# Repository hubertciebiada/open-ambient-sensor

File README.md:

<h1 align="center">OAS — Open Ambient Sensor</h1>

<p align="center">
  <b>DIY multi-sensor environmental monitor for indoor spaces.</b><br>
  Measures air quality and presence; mounts on a standard wall-recessed electrical box; runs ESPHome and integrates natively with Home Assistant.
</p>

<p align="center">

</p>

https://github.com/user-attachments/assets/d60150c3-3ed5-4fff-b437-b9b54c48e413

---

## Status

**v0.54 — manufactured, bench-validated and in use.** Boards of this revision were fabricated and SMT-assembled at JLCPCB, brought up on the bench with a repeatable per-unit check, and run in a multi-unit deployment as the sensor input for Home Assistant HVAC automations. Working on the delivered hardware: the 24 V power chain, the Sensirion SEN66 (CO₂ / PM / VOC / NOx / T / RH, with Sensirion's STAR temperature compensation running inside the module), the HLK-LD2410C presence radar including stillness detection, the LED ring, Wi-Fi / OTA / native Home Assistant API, the Bluetooth proxy and the on-device web dashboard. The firmware reports `project_version: v0.54`, matching the version printed on the silkscreen. The design is fully script-generated and verified: `build.py` 35/35 stages PASS, DRC 0 violations / 0 unconnected, JLCPCB DFM 0 Danger on both the bare-board and assembly checks. The production files for this revision are attached to the [GitHub release](https://github.com/hubertciebiada/open-ambient-sensor/releases). See [`CLAUDE.md`](./CLAUDE.md) for the design rationale, hard constraints and the lessons learned along the way.

---

## Can I build one today?

**Yes — this revision has been built and works.** What to know before ordering:

- **The production files are in the repo.** [`hardware/output/jlcpcb/`](./hardware/output/jlcpcb/) holds the gerber + drill bundle, the BOM and the CPL files for JLCPCB SMT assembly (also attached to the GitHub release); they are regenerated and verified by the 35-stage pipeline on every build. Follow the ordering workflow in [`CLAUDE.md`](./CLAUDE.md#jlcpcb-ordering-workflow-distilled-from-v040-saga) — in particular the pre-payment Assembly Order cross-check, which has caught wrong-part substitutions more than once.
- **Seven components are hand-soldered after assembly** — the 24 V terminal block, the two ESP32-C6-DevKitM-1 socket headers, the LD2410C header and the three THT capacitors — and the SEN66 is attached with its JST GH lead and zip ties. Flashing and Home Assistant onboarding are documented in [`firmware/README.md`](./firmware/README.md).
- **Cost positioning.** OAS deliberately sits above bargain-DIY BOM cost: a calibrated Sensirion SEN66 combo sensor, an mmWave radar with stillness detection, and a commercial-grade injection-moulded enclosure are all premium choices made on purpose — see [Design philosophy](#design-philosophy). If lowest possible cost is your priority, other open-source projects optimise for that instead.

**Known limitations** (findings on the built units):

- **The LED ring effect is weaker than designed.** For the SEN66 to read correctly inside the enclosure, an air duct has to guide room air from the perforated cover to the sensor inlet, and that duct sits in front of part of the ring. The duct is not part of this repository yet.
- **Detecting a sleeping person relies on the presence timeout**, not on the radar's still-target thresholds — see the notes in [`firmware/esphome/packages/presence.yaml`](./firmware/esphome/packages/presence.yaml).
- **v0.51 prototype boards** need the pin overrides in [`firmware/esphome/HARDWARE-COMPAT-v0.51.md`](./firmware/esphome/HARDWARE-COMPAT-v0.51.md); v0.54 boards run the firmware defaults.

A consolidated step-by-step build guide is not written yet; open work is tracked in the [TODO list](./CLAUDE.md#open-work--todo) in `CLAUDE.md`.

---

## What it measures

- **Air quality** — CO₂, PM1 / PM2.5 / PM4 / PM10, VOC index, NOx index, temperature, relative humidity (Sensirion SEN66)
- **Occupancy / presence** — mmWave radar with stillness detection (HiLink HLK-LD2410C)

## Additional features

- 7× SK6812-SIDE RGB AQI ring with breathing effect (7 LEDs on an 8-slot ring; D13 vacated for the J1 24 V terminal); colour reflects an aggregated air-quality index
- **Bluetooth proxy** — extends BLE range across the deployment for Home Assistant BLE integrations
- Qwiic / STEMMA QT expansion port — future sensors without a PCB respin

---

## Design philosophy

The open-source DIY space offers many indoor-air-quality projects. Most optimise aggressively for cost. **OAS holds two priorities non-negotiable**, even when the trade-off is a higher per-unit BOM than the cheapest alternatives:

1. **Measurement quality.** Sensor choices favour accuracy and long-term stability over price.
2. **Aesthetic acceptability.** The device is meant to live in inhabited rooms; a commercial-grade injection-moulded enclosure replaces the typical 3D-printed box.

Both compromises (cheap-but-inaccurate, accurate-but-ugly) are rejected. See [`CLAUDE.md`](./CLAUDE.md) for the full rationale and the hard constraints any change must clear.

---

## Hardware overview

| Function | Component | Interface |
|---|---|---|
| MCU | ESP32-C6-DevKitM-1-N4 (EAN 5904422385651) | 2× USB-C on module |
| Air quality combo | Sensirion SEN66-SIN-T | I²C (JST GH 6-pin cable) |
| Presence | HiLink HLK-LD2410C | UART @ 256000 baud |
| Visual indicator | 7× SK6812-SIDE side-emit ring (Ø26 mm base pitch, 8 slots with D13 vacated for J1) | 1-wire WS281x on GPIO 8 |
| Power input | 24 V DC terminal block + TVS + PTC + reverse-polarity P-FET | — |

**Enclosure:** SZOMK AK-N-94 (Ø128 mm perforated white ABS). PCB is a **Ø120 mm D-shape** with a flat chord along the bottom edge. Mounts on a standard wall-recessed electrical box (60 mm screw pitch).

Authoritative module metadata (EAN, MPN, datasheet URLs, derived dimensions) lives in [`hardware/kicad/boardgen/_project.py::EXTERNAL_MODULES`](./hardware/kicad/boardgen/_project.py). Pinout is in [`boardgen/_project.py::GPIO_ASSIGNMENTS`](./hardware/kicad/boardgen/_project.py). Full design rationale and hard constraints: [`CLAUDE.md`](./CLAUDE.md).

---

## Repository layout

```
open-ambient-sensor/
├── README.md                       # this file
├── CLAUDE.md                       # design rationale, hard constraints, working conventions
├── GPLv3-LICENSE.md
├── .gitignore
├── media/                          # promo video (oas-promo.mp4) + README photos (oas-*.webp)
├── firmware/
│   ├── README.md                   # flashing + Home Assistant integration
│   ├── esphome/
│   │   ├── oas.yaml                # top-level ESPHome config
│   │   ├── packages/               # core / leds / air-quality / presence / bt-proxy
│   │   └── examples/               # anonymized per-device override examples
│   ├── tools/                      # bringup_check.py — repeatable per-unit bench check
│   └── secrets.yaml.example
└── hardware/
    ├── kicad/
    │   ├── build.py                # THE single entrypoint — emits sources + runs the 35-stage pipeline
    │   ├── boardgen/               # source of truth — generators for every .kicad_* file
    │   ├── pipeline/               # 35 verification/export stages (generic / oas / jlcpcb)
    │   ├── tests/                  # unit-test suite (pytest; run by stage 16 of build.py)
    │   ├── tools/                  # manual-trigger scripts (route extract, DFM upload, jlcparts cache)
    │   ├── oas_routes.py           # routing snapshot (replayed onto the generated PCB)
    │   ├── lcsc_mapping.py         # SMD BOM — LCSC SKU source of truth
    │   └── oas.kicad_*             # generated KiCad project files (derived artefacts — never hand-edit)
    ├── renders/                    # generated previews (PNG + SVG, visual changelog)
    ├── photos/                     # photos of built units (EXIF stripped)
    └── output/                     # production deliverables (ibom + jlcpcb/ ZIP + BOM + 2× CPL)
```

---

## Rebuilding the design from source

The KiCad project is **fully script-generated**. The `.kicad_pcb` / `.kicad_sch` / `.kicad_pro` / library files are derived artefacts — **never hand-edit them**; the next build overwrites every edit. The source of truth lives in [`hardware/kicad/boardgen/`](./hardware/kicad/boardgen/) (Python generators), [`lcsc_mapping.py`](./hardware/kicad/lcsc_mapping.py) (SMD BOM), and [`oas_routes.py`](./hardware/kicad/oas_routes.py) (routing snapshot).

```sh
cd hardware/kicad
python build.py
```

`build.py` is the only top-level entrypoint. It regenerates every KiCad source file bit-identically (deterministic v5 UUIDs — an unchanged tree produces an empty `git diff`) and then runs the full 35-stage verification pipeline: DRC, ERC, determinism self-check, analytical DC / ampacity / boot-strap / thermal / I²C-rise-time checks, ngspice SPICE simulations (buck soft-start, IEC 61000-4-5 surge, reverse polarity), unit tests, renders, and the vendor export stages that produce the JLCPCB deliverables. Any stage failure aborts the build.

**Requirements:**

- Python 3.11+
- KiCad 10 with `kicad-cli` on `PATH`
- `pip install mypy pytest cairosvg pygerber`
- `git submodule update --init` (kicad-skip, InteractiveHtmlBom, jlcparts, and other tools under `hardware/kicad/third_party/`)
- One-time jlcparts offline cache for the LCSC part-verification stage: `python hardware/kicad/tools/setup_jlcparts_cache.py` (~2 GiB download, expands to a local SQLite cache)

ngspice and the vendor SPICE models are downloaded automatically into a gitignored `.tmp/` directory on first run. Individual pipeline stages are independently runnable for debugging (e.g. `python pipeline/generic/03_drc.py`), but a committable state always comes from a full `build.py` pass.

---

## Contributing

Contributions are welcome once the design stabilises. Any change must clear both design pillars (measurement quality, aesthetic acceptability) and the hard constraints listed in [`CLAUDE.md`](./CLAUDE.md#hard-constraints-do-not-violate-without-an-explicit-documented-decision).

**This is a public repository** — see the [public-repository rules](./CLAUDE.md#-public-repository-rules) for the anonymisation and third-party-IP requirements that apply to every committed file.

---

## License

GNU General Public License v3.0 — see [`GPLv3-LICENSE.md`](./GPLv3-LICENSE.md).

---

## References

- AirGradient ONE (open-source inspiration): <https://github.com/airgradienthq/arduino>
- Sensirion SEN66 product page: <https://sensirion.com/products/catalog/SEN66>
- HiLink LD2410 documentation: <https://www.hlktech.net>
- ESPHome documentation: <https://esphome.io>
- JLCPCB component library: <https://jlcpcb.com/parts>

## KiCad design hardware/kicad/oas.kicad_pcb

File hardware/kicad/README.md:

# KiCad project — OAS

Base KiCad 10.x project for the Open Ambient Sensor PCB. **Preliminary draft** — board outline and mounting holes only; schematic and routing are TODO.

## How to open

1. Install **KiCad 10.0.2** or newer from <https://www.kicad.org/download/>.
2. Open `oas.kicad_pro` in KiCad.
3. The project will load:
   - `oas.kicad_sch` — empty schematic (placeholder)
   - `oas.kicad_pcb` — board outline + 3 mounting holes on `Edge.Cuts`
   - Local footprint library `oas` (just the custom `MountingHole_3.8mm_M3` for now)

When KiCad opens the PCB the first time it may ask you to migrate the project — accept; the file format is already at v10.

## What's already in `oas.kicad_pcb`

- **Board outline on `Edge.Cuts`:** Ø120 mm circular arc (R=60 mm) + flat chord 82.65 mm (precise: 82.6545 mm from the DXF). Origin (0, 0) is the centre of the circle. The flat chord sits at Y≈+43.50 — in KiCad's coordinate convention (Y grows downward on screen), that's the visual **bottom** of the board.
- **3× M3 mounting holes (NPTH)**: Ø3.8 mm drill, no copper pad, on a pitch circle Ø110 mm. Positions:
  - H1: (+47.631, +27.500) — bottom-right
  - H2: (−47.631, +27.500) — bottom-left
  - H3: (0, −55.000) — top (opposite the chord)
- **Cable pass-through hole**: Ø12 mm circular cut-out on `Edge.Cuts` at the PCB centre (origin) — 24 V power wires enter from the rear of the case, pass through to a terminal block on the front side. Sized for 3× 1.5 mm² conductors with margin.
- **5× connector cutout keepout zones** on F.Cu + B.Cu blocking tracks, vias, pads, copperpour and footprints — one per case-wall cutout. See [`../case/README.md`](../case/README.md#connector-cutouts-in-the-case-wall-along-the-flat-chord) for the exact dimensions.
- **5× rectangle markers on `Dwgs.User`** labelled `C1…C5` with their size — visual reference for connector placement in pcbnew (this layer is not plotted).
- **Clock-face sector markers on `Dwgs.User`**: 3 dashed radial lines (12:00, 03:00, 09:00 azimuths) + 3 labels (`POWER`, `MCU`, `SENSORS`). Sectors map onto the hierarchical schematic sheets and define where each subsystem's components belong on the PCB. See [`../../docs/ARCHITECTURE.md`](../../docs/ARCHITECTURE.md#pcb-sector-layout) for the rationale.
- **Stackup:** 2-layer, FR-4 1.6 mm, 1 oz (35 µm) copper, white solder mask, black silkscreen, HASL lead-free finish.
- **JLCPCB-compatible design rules:** min trace/space 0.15 mm, min via 0.5 mm Ø / 0.3 mm drill, min hole 0.3 mm, edge clearance 0.3 mm.

## Material and stackup decisions (and why)

You said you've never done a PCB — here's the rationale for every choice. Anything below can be changed in `oas.kicad_pro` (design rules) or in `oas.kicad_pcb`'s `(setup (stackup ...))` block.

| Choice | Value | Why |
|---|---|---|
| **Layer count** | 2 | Sufficient for ESP32-C6 + I²C + UART + WS2812. 4-layer is overkill for this design and costs ~1.5× more at JLCPCB. Can be bumped if noise becomes an issue in v2. |
| **Board thickness** | 1.6 mm | JLCPCB default, free; mechanically rigid for a Ø120 mm board. |
| **Material** | FR-4, Tg ≥ 130 °C | JLCPCB Standard FR-4 (Tg 135–150). Fine for 24 V DC, low currents, no thermal stress. |
| **Copper weight** | 1 oz (35 µm) | JLCPCB default, free. Adequate for ≤ 3 A peak on power traces. |
| **Solder mask colour** | **White** | **Aesthetic match with the white perforated ABS enclosure** (CLAUDE.md design pillar 2 — aesthetic acceptability). White mask at JLCPCB costs a small premium over green but is worth it here. |
| **Silkscreen colour** | Black | Standard, high contrast on white mask. |
| **Surface finish** | HASL lead-free | JLCPCB default, free. ENIG would look nicer but adds ~$15 to a small batch and the pads aren't visible in the enclosure anyway. |
| **Min trace / space** | 0.15 mm (6 mil) | JLCPCB Standard rules. Going finer (4 mil) costs more without benefit on this design. |
| **Min via** | 0.5 mm Ø / 0.3 mm drill | JLCPCB Standard rules. |
| **Min hole** | 0.3 mm | JLCPCB Standard rules. |
| **Edge clearance** | 0.3 mm | JLCPCB tolerance for the routed board edge. |

If you want a quote, upload the gerbers (once generated — TODO) to <https://jlcpcb.com>. With these defaults the board falls in JLCPCB's cheapest tier (~$2–5 per unit at quantity 5–10, plus shipping).

## How to regenerate everything

The single entry point for any change is **`regenerate.py`**:

```bash
python regenerate.py
```

That script:
1. runs `generate.py` to rebuild every KiCad source file from the Python geometry constants;
2. runs `kicad-cli pcb drc` and `kicad-cli sch erc` (aborts on any error / warning);
3. re-renders every preview into `renders/`:
   - `2d-top.{svg,png}` — production-style top view (F.Cu + masks + silks + Edge.Cuts)
   - `2d-cutouts.{svg,png}` — Edge.Cuts + Dwgs.User cutout markers + F.Cu (no-go zones)
   - `2d-bottom.{svg,png}` — mirrored bottom view
   - `3d-top.png` — raytraced 3D render (~15 s)
   - `_drc.rpt` / `_erc.rpt` — text reports of DRC / ERC results

Typical run time: ~30 s (dominated by the 3D render).

**UUIDs are deterministic** (v5 namespaced under the OAS project), so re-running with no source changes produces a **bit-identical** `oas.kicad_pcb` — `git diff` is empty unless geometry actually changed.

### When to use `generate.py` directly

Almost never. `regenerate.py` is the canonical entry point. The one case where `generate.py` alone makes sense is if you want a quick smoke test of a `generate.py` change without paying for the 3D render.

### Changing geometry

Edit the constants at the top of `generate.py`:

- `R_OUTLINE`, `CHORD`, `HALF_CHORD` — PCB outline
- `HOLE_DIAMETER`, `PAD_DIAMETER`, `R_PITCH` — mounting holes
- `CUTOUTS` — list of `(name, x_min, x_max, y_min, y_max)` for the case-wall cutouts
- `PAGE_CENTRE_X`, `PAGE_CENTRE_Y` — page-space offset (you almost never want to change this)

For structural / material changes (layer count, stackup, design rules, footprint definitions), edit the relevant generator function further down in `generate.py`.

After editing, run `python regenerate.py` and commit the resulting diff (sources + KiCad files + renders together — they are one logical change).

The geometry constants currently match the SZOMK AK-N-94 manufacturer DXF (see [`../case/README.md`](../case/README.md)).

## Layout strategy

The PCB orientation in KiCad matches the physical wall-mount orientation:

- **Bottom edge** (flat chord, Y=+43.5) — connector strip: 24 V terminal, SWD header (unpopulated), Qwiic expansion (no external USB-C — DevKitM-1's onboard USB-C accessible before sealing)
- **Top half / sensors region** — SEN66 (PCB-mounted, face-up), LD2410 mmWave radar, NT3H2211 + NFC antenna
- **Middle** — MCU (ESP32-C6-DevKitM-1-N4, antenna toward 12:00) and status LED (onboard NeoPixel on GPIO 8)
- **Adjacent to the 24 V terminal** — power section (TVS, PTC, buck converters)

Thermal-isolation slots (1.5 mm milled gaps in FR4) will separate the Power, MCU and peripheral zones — to be drawn on `Edge.Cuts` once the floorplan is finalised.

See [`../../docs/ARCHITECTURE.md`](../../docs/ARCHITECTURE.md) for the full pinout and thermal/layout rationale.

## What you'll do next (TODO)

Roughly in order:

1. **Schematic** (`oas.kicad_sch`) — place the ESP32-C6-DevKitM-1-N4 (EAN 5904422385651), SEN66 connector, LD2410 connector, NT3H2211, buck converters, TVS, PTC, 24 V terminal block, SWD/UART recovery header (unpopulated), Qwiic connector. No external USB-C and no external WS2812 — both are on the DevKitM-1 module. Net them up.
2. **Footprints** — assign footprints in the schematic (most parts are stock in `Connector_*`, `Sensor_*`, `Package_DFN_QFN`, `Package_SO`). The mounting holes already use the custom `oas:MountingHole_3.8mm_M3`.
3. **PCB layout** — update PCB from schematic, then place parts respecting:
   - 17 mm front-side height limit (5 mm back-side with washer-lifted PCB)
   - SEN66 is **not on the PCB** (mounted on cover, JST GH cable to a header)
   - Connector strip along the flat chord
   - Thermal-isolation slots between zones
4. **Run DRC** at JLCPCB rules; fix violations.
5. **3D view** — check no component exceeds 17 mm.
6. **Generate gerbers** (`File → Fabrication Outputs → Gerbers`) into `../gerbers/`.

## Files in this directory

```
hardware/kicad/
├── README.md                                    # this file
├── generate.py                                  # script that built the project
├── oas.kicad_pro                                # project (design rules, net classes)
├── oas.kicad_sch                                # empty schematic
├── oas.kicad_pcb                                # PCB with outline + mounting holes
├── fp-lib-table                                 # registers the "oas" footprint library
├── sym-lib-table                                # empty symbol library table
└── libraries/
    └── oas.pretty/
        └── MountingHole_3.8mm_M3.kicad_mod      # custom footprint matching the DXF
```

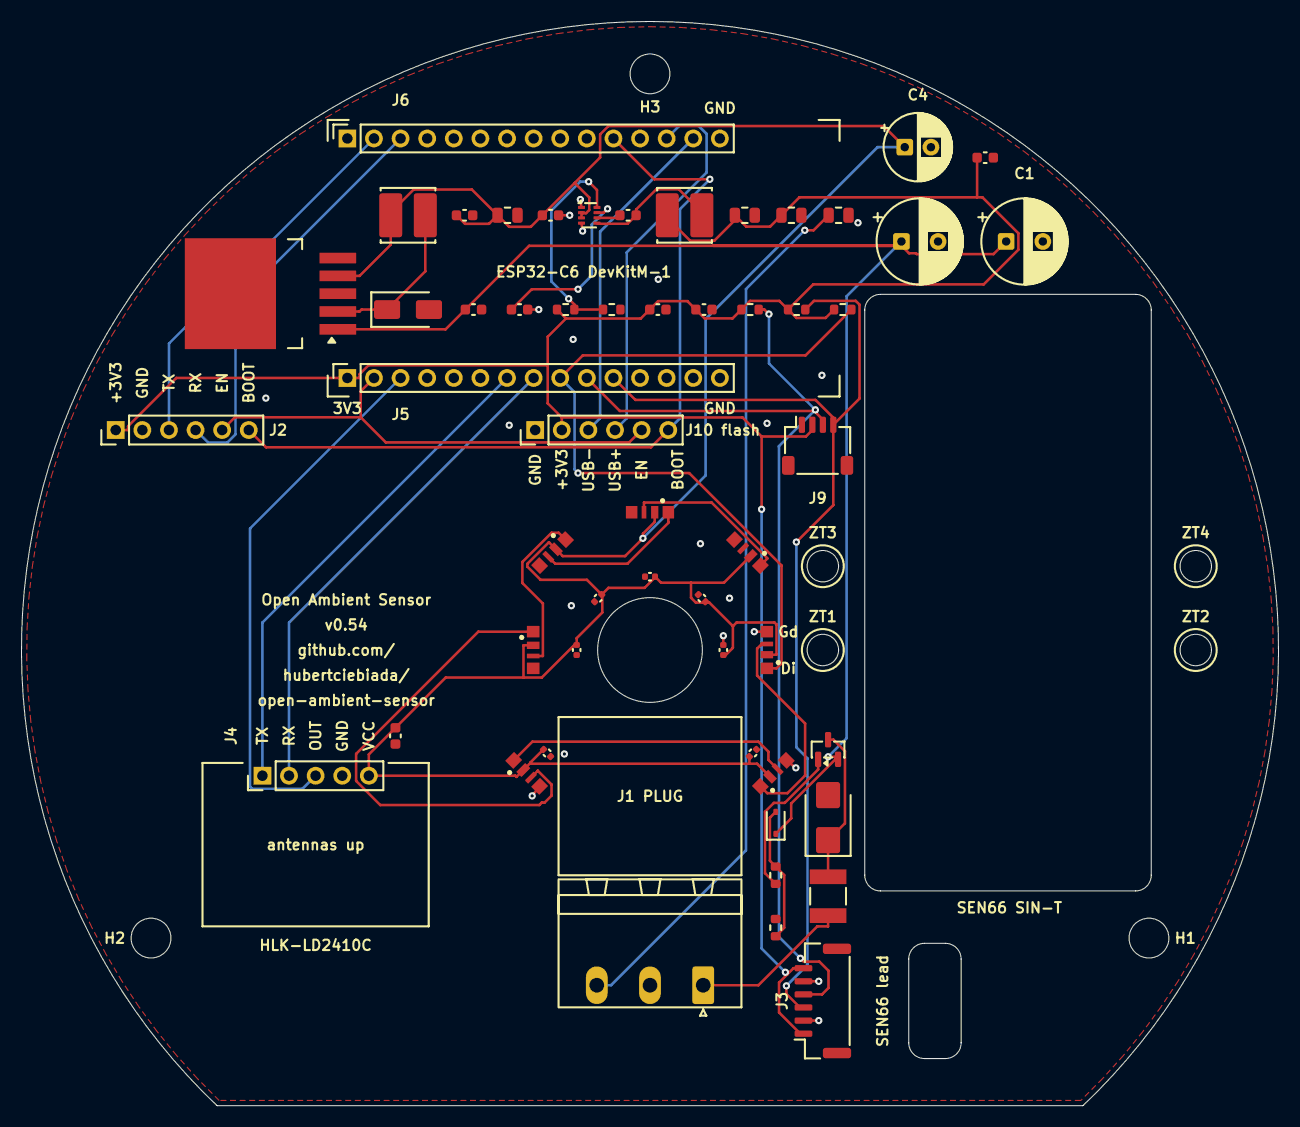
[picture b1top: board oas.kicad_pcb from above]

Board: 2 copper layers, 120.0 x 103.5 mm, 64 parts (0 on the bottom side), 32 nets.

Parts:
C1, C3: 100uF/50V; CP_Radial_D8.0mm_P3.50mm
C2: 10nF Y2; C_0805_2012Metric
C4: 220uF/10V; CP_Radial_D6.3mm_P2.50mm
C5, C9: 10uF; C_0805_2012Metric
C6: 22uF; C_0805_2012Metric
C7, C10, C11, C13, C14, C15, C16, C17: 100nF; C_0603_1608Metric
C8: 47nF; C_0603_1608Metric
C20, C21, C23, C24, C25, C26, C27: 100nF; C_0402_1005Metric
D1: SMBJ24A; D_SMB
D2: SS14; D_SMA
D3: 10V Zener 200mW; D_SOD-323
D11, D12, D14, D15, D16, D17, D18: SK6812-SIDE
F1: 1812L075/33DR; Fuse_1812L_4532Metric
H1, H2, H3: MountingHole_3.8mm_M3_NPTH; MountingHole_3.8mm_M3
J1: Phoenix_MSTBA_2,5/3-G-5,08 (24V input); PhoenixContact_MSTBA_2,5_3-G-5,08_1x03_P5.08mm_Horizontal
J2: UART/Boot Recovery (DNP); PinHeader_1x06_P2.54mm_Vertical
J3: JST SM06B-GHS-TB (SEN66 connector); JST_GH_SM06B-GHS-TB_1x06-1MP_P1.25mm_Horizontal
J4: 1x5 P2.54mm header (HLK-LD2410C); PinHeader_1x05_P2.54mm_Vertical
J5: ESP32 row A (pins 1..15, antenna-side row); PinSocket_1x15_P2.54mm_Vertical
J6: ESP32 row B (pins 16..30, USB-side row); PinSocket_1x15_P2.54mm_Vertical
J9: JST SM04B-SRSS-TB (Qwiic / Stemma QT); JST_SH_SM04B-SRSS-TB_1x04-1MP_P1.00mm_Horizontal
J10: Native-USB recovery (DNP); PinHeader_1x06_P2.54mm_Vertical
L1: 33uH; L_Cenker_CKCS5040
L2: 2.2uH; L_Cenker_CKCS5040
LDR1: LD2410_Mechanical_Reference
MOD1: oas:ESP32-C6-DevKitM-1_Reference; ESP32-C6-DevKitM-1_Reference
Q1: AO3401A; SOT-23
R1: 100k 1%; R_0603_1608Metric
R2: 100k; R_0603_1608Metric
R3: 30.9k; R_0603_1608Metric
R4: 1k; R_0603_1608Metric
R5, R6: 4.7k; R_0603_1608Metric
R7: 10k; R_0603_1608Metric
SENS1: SEN66_Mechanical_Reference
U1: LM2596S-5.0; TO-263-5_LM2596
U2: TPS62933; SOT-583-8
ZT1, ZT2, ZT3, ZT4: ZipTieHole_3mm_NPTH

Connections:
+3V3: C6.1, C9.1, C10.1, C16.1, C17.1, J2.1, J3.1, J3.6, J5.1, J9.2, J10.2, L2.1, R2.1, R5.1, R6.1, R7.1
+5V: C4.1, C5.1, C11.1, C14.1, C15.1, C20.1, C21.1, C23.1, C24.1, C25.1, C26.1, C27.1, D11.2, D12.2, D14.2, D15.2, D16.2, D17.2, D18.2, J4.5, L1.1, U1.4, U2.2, U2.3
+24V: C1.1, C3.1, C13.1, D3.1, Q1.2, U1.1
/IO/BOOT: J2.6, J6.11, J10.6
/IO/EN: J2.5, J5.2, J10.5
/IO/I2C_SCL: J3.3, J5.11, J9.4, R6.2
/IO/I2C_SDA: J3.4, J5.10, J9.3, R5.2
/IO/USB_DM: J6.14, J10.3
/IO/USB_DP: J6.13, J10.4
/MCU/LD2410_OUT: J4.3, J5.3
/MCU/LD2410_UART_RX: J4.1, J5.7
/MCU/LD2410_UART_TX: J4.2, J5.8
/MCU/UART_RX: J2.4, J6.3
/MCU/UART_TX: J2.3, J6.2
/MCU/WS2812_DIN: D11.1, J5.9, R7.2
Earth_Protective: C2.1, J1.3
GND: C1.2, C2.2, C3.2, C4.2, C5.2, C6.2, C8.2, C9.2, C10.2, C11.2, C13.2, C14.2, C15.2, C16.2, C17.2, C20.2, C21.2, C23.2, C24.2, C25.2, C26.2, C27.2, D1.2, D2.2, D11.4, D12.4, D14.4, D15.4, D16.4, D17.4, D18.4, J1.2, J2.2, J3.2, J3.5, J4.4, J5.13, J5.15, J6.1, J6.12, J6.15, J9.1, J10.1, R1.2, R3.2, U1.3, U1.5, U2.1, U2.4
unnamed: D1.1, F1.2, Q1.3
unnamed: D2.1, L1.2, U1.2
unnamed: D3.2, R1.1, R4.2
unnamed: D11.3, D12.1
unnamed: D12.3, D14.1
unnamed: D14.3, D15.1
unnamed: D15.3, D16.1
unnamed: D16.3, D17.1
unnamed: D17.3, D18.1
unnamed: F1.1, J1.1
unnamed: Q1.1, R4.1
unnamed: C7.1, U2.6
unnamed: R2.2, R3.1, U2.8
unnamed: C8.1, U2.7
unnamed: C7.2, L2.2, U2.5

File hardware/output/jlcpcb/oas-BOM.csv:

Comment,Designator,Footprint,Manufacturer,MPN,LCSC Part #,JLCPCB_Library,Qty
47nF,C8,C_0603_1608Metric,Samsung Electro-Mechanics,CL10B473KB8NNNC,C1622,Basic,1
100nF,"C7,C10,C11,C13,C14,C15,C16,C17",C_0603_1608Metric,Yageo,CC0603KRX7R9BB104,C14663,Basic,8
100nF,"C20,C21,C23,C24,C25,C26,C27",C_0402_1005Metric,Samsung Electro-Mechanics,CL05B104KO5NNNC,C1525,Basic,7
1k,R4,R_0603_1608Metric,UNI-ROYAL (Uniroyal Elec),0603WAF1001T5E,C21190,Basic,1
100k 1%,"R1,R2",R_0603_1608Metric,UNI-ROYAL (Uniroyal Elec),0603WAF1003T5E,C25803,Basic,2
100uF 50V,"C1,C3",CP_Radial_D8.0mm_P3.50mm,,,,THT (hand-solder),2
10k 1%,R7,R_0603_1608Metric,UNI-ROYAL (Uniroyal Elec),0603WAF1002T5E,C25804,Basic,1
10nF Y2,C2,C_0805_2012Metric,Murata Electronics,GRM21BR72A103KA01L,C97925,Extended,1
10uF 25V,"C5,C9",C_0805_2012Metric,Samsung Electro-Mechanics,CL21A106KAYNNNE,C15850,Basic,2
10V Zener 200mW,D3,D_SOD-323,Nanjing Semtech Electronics,BZT52C10S,C19334,Extended,1
1x15 P2.54 mm female socket (ESP32 J1 antenna-side row),J5,PinSocket_1x15_P2.54mm_Vertical,,,,THT (hand-solder),1
1x15 P2.54 mm female socket (ESP32 J3 USB-side row),J6,PinSocket_1x15_P2.54mm_Vertical,,,,THT (hand-solder),1
"1x5 P2.54mm through-hole header (HLK-LD2410C daughterboard, soldered)",J4,PinHeader_1x05_P2.54mm_Vertical,,,,THT (hand-solder),1
2.2uH 2A,L2,L_Cenker_CKCS5040,CENKER,CKCS5040-2.2uH/M,C354602,Extended,1
220uF 10V,C4,CP_Radial_D6.3mm_P2.50mm,,,,THT (hand-solder),1
22uF 10V,C6,C_0805_2012Metric,Samsung Electro-Mechanics,CL21A226MAQNNNE,C45783,Basic,1
30.9k 1%,R3,R_0603_1608Metric,UNI-ROYAL (Uniroyal Elec),0603WAF3092T5E,C23022,Extended,1
33uH 2A,L1,L_Cenker_CKCS5040,CENKER,CKCS5040-33uH/M,C354612,Extended,1
4.7k 1%,"R5,R6",R_0603_1608Metric,UNI-ROYAL (Uniroyal Elec),0603WAF4701T5E,C23162,Basic,2
AO3401A,Q1,SOT-23,Alpha & Omega Semiconductor,AO3401A,C15127,Extended,1
JST SH SM04B-SRSS-TB (Qwiic / Stemma QT),J9,JST_SH_SM04B-SRSS-TB_1x04-1MP_P1.00mm_Horizontal,JST Sales America,SM04B-SRSS-TB(LF)(SN),C160404,Extended,1
"JST SM06B-GHS-TB (SEN66-SIN-T, MPN 3.001.030; TME/Mouser)",J3,JST_GH_SM06B-GHS-TB_1x06-1MP_P1.25mm_Horizontal,JST Sales America,SM06B-GHS-TB(LF)(SN),C133065,Extended,1
LM2596S-5.0,U1,TO-263-5_LM2596,Texas Instruments,LM2596S-5.0/NOPB,C116713,Extended,1
"Phoenix_MSTBA_2,5/3-G-5,08",J1,"PhoenixContact_MSTBA_2,5_3-G-5,08_1x03_P5.08mm_Horizontal",,,,THT (hand-solder),1
PTC 750mA / 33V,F1,Fuse_1812L_4532Metric,Littelfuse,1812L075/33DR,C151170,Extended,1
SK6812-SIDE,"D11,D12,D14,D15,D16,D17,D18",SK6812-SIDE,OPSCO Optoelectronics,SK6812SIDE-A,C5378721,Extended,7
SMBJ24A,D1,D_SMB,Brightking,SMBJ24A,C87268,Basic,1
SS14,D2,D_SMA,MDD (Microdiode Semiconductor),SS14,C2480,Basic,1
TPS62933,U2,SOT-583-8,Texas Instruments,TPS62933DRLR,C3200405,Extended,1

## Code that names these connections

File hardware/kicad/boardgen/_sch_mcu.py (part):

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      the +3V3 bus / R5 / R6 / C9 / C17 wiring drop in unchanged.

      J2 (UART/Boot recovery, DNP) — rotated to angle=180 in v0.21
      so its UART TX/RX pin row aligns with J6's UART_TX (pin 2 at
      Y=125.73) / UART_RX (pin 3 at Y=123.19). At angle=180 the J2
      pin order in screen Y is REVERSED vs angle=0: pin 1 (+3V3) at
      the BOTTOM, pin 6 (BOOT) at the TOP.

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      J5 (DevKitM-1 J1, antenna-side header)
        J5.1   3V3                              → +3V3 bus
        J5.2   RST                              → hier label "EN"
        J5.3   GPIO2                            → hier label "LD2410_OUT"
        J5.4   GPIO3                            → no_connect (spare)
        J5.5   GPIO4   (strap MTMS)             → no_connect
        J5.6   GPIO5   (strap MTDI)             → no_connect
        J5.7   GPIO0                            → hier label "LD2410_UART_RX"
        J5.8   GPIO1                            → hier label "LD2410_UART_TX"
        J5.9   GPIO8   (strap boot, onboard LED)→ hier label "WS2812_DIN"
        J5.10  GPIO6                            → hier label "I2C_SDA"
        J5.11  GPIO7                            → hier label "I2C_SCL"
        J5.12  GPIO14                           → no_connect (spare)
        J5.13  GND                              → GND
        J5.14  5V                               → no_connect (powering 3V3 only)
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
      J6 (DevKitM-1 J3, USB-side header)
        J6.1   GND                              → GND
        J6.2   GPIO16  (U0TXD console)          → local label "UART_TX"
        J6.3   GPIO17  (U0RXD console)          → local label "UART_RX"
        J6.4   GPIO23                           → no_connect (spare)
        J6.5   GPIO22                           → no_connect (spare)
        J6.6   GPIO21                           → no_connect (spare)
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        J6.10  GPIO15  (strap)                  → no_connect
        J6.11  GPIO9   (strap, BOOT button)     → hier label "BOOT"
        J6.12  GND                              → GND
        J6.13  GPIO13  (USB D+)                 → hier label "USB_DP"
        J6.14  GPIO12  (USB D-)                 → hier label "USB_DM"
        J6.15  GND                              → GND

    Inter-sheet nets exported via hierarchical_label (matching sheet
    ports are declared on the root sheet's MCU sheet block):
      I2C_SDA, I2C_SCL    → sensors sub-sheet + io sub-sheet (Qwiic)
      LD2410_UART_TX/_RX  → sensors sub-sheet (LD2410C, J4 pins 2 / 1)
      LD2410_OUT          → sensors sub-sheet
      USB_DM, USB_DP      → io sub-sheet (J10 native-USB recovery header)
      EN                  → io sub-sheet (J10 chip-enable / reset pin)
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    EN net with the IO sub-sheet's J10 recovery EN pin):
      J2.1  +3V3
      J2.2  GND
      J2.3  UART_TX        — taps J6 pin 2 UART_TX
      J2.4  UART_RX        — taps J6 pin 3 UART_RX
      J2.5  EN             — hier label, joins J5 pin 2 RST
      J2.6  BOOT           — hier label, joins J6 pin 11 BOOT

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    # Per-signal pin-tip resolution (single source of truth).
    J5_3V3_Y    = j5_pin_y(J5_SIGNAL_PIN["3V3"])         # 92.71
    J5_RST_Y    = j5_pin_y(J5_SIGNAL_PIN["RST"])         # 95.25
    J5_LDR_Y    = j5_pin_y(J5_SIGNAL_PIN["LD2410_OUT"])  # 97.79
    J5_LD_RX_Y  = j5_pin_y(J5_SIGNAL_PIN["LD2410_UART_RX"])  # 107.95
    J5_LD_TX_Y  = j5_pin_y(J5_SIGNAL_PIN["LD2410_UART_TX"])  # 110.49
    J5_WS_Y     = j5_pin_y(J5_SIGNAL_PIN["WS2812_DIN"])  # 113.03
    J5_SDA_Y    = j5_pin_y(J5_SIGNAL_PIN["I2C_SDA"])     # 115.57
    J5_SCL_Y    = j5_pin_y(J5_SIGNAL_PIN["I2C_SCL"])     # 118.11
    J6_TX_Y     = j6_pin_y(J6_SIGNAL_PIN["UART_TX"])     # 125.73
    J6_RX_Y     = j6_pin_y(J6_SIGNAL_PIN["UART_RX"])     # 123.19
    J6_BOOT_Y   = j6_pin_y(J6_SIGNAL_PIN["BOOT"])        # 102.87
    J6_USB_DP_Y = j6_pin_y(J6_SIGNAL_PIN["USB_DP"])      # 97.79
    J6_USB_DM_Y = j6_pin_y(J6_SIGNAL_PIN["USB_DM"])      # 95.25

    # ===== C9: bulk decoupling, 10uF ceramic (non-polarized) =====
    # Reviewer raised C9's voltage rating from 10 V to 16 V (v0.5):
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    R5_Y = 80.01                    # body center; pin1 = 76.20, pin2 = 83.82
    R6_Y = 80.01

    # ===== R7: GPIO 8 (WS2812_DIN) boot-strap pull-up, 10 kΩ 0603 =====
    # v0.22 — new in this revision (Task #18 M2). ESP32-C6 GPIO 8 is a
    # strap pin that must be HIGH at boot for SPI flash boot mode. The
    # DevKitM-1's onboard "pull-up" relies on VCC_5V powering the onboard
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
    # ===== J2: UART/Boot recovery header, 6-pin, DNP =====
    # v0.21: rotated to angle=180 so its pin 3 (TX) / pin 4 (RX) order
    # matches J6's reversed pin Y order (J6.2 UART_TX at BOTTOM
    # Y=125.73, J6.3 UART_RX above at Y=123.19). With angle=180, J2
    # pin 1 (+3V3) lands at the BOTTOM (anchor_y + 5.08), pin 6 (BOOT)
    # at the TOP (anchor_y - 7.62). Pin tips on the RIGHT at
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    # ===== Hierarchical-label columns =====
    # LEFT-edge labels (sensor-bound nets): X=119.38.
    HLABEL_LEFT_X = 119.38
    # RIGHT-edge labels: X=222.25 (USB_DP, USB_DM — the console UART_TX /
    # UART_RX labels used to sit here too, until they stopped leaving this
    # sheet and became local labels at the J2 stub column).
    HLABEL_RIGHT_X = 222.25

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    parts.append(_sch_wire(J6_PIN_X, J6_TX_Y, CONSOLE_LABEL_X, J6_TX_Y, "tx-bus"))
    parts.append(_sch_junction(J2_PIN_X, j2_tx_y, "tx-j2-tap"))
    parts.append(_sch_local_label(
        name="UART_TX", x=CONSOLE_LABEL_X, y=J6_TX_Y,
        angle=0, justify="left", uuid_tag="uart-tx-console",
    ))
    # RX: straight east from J6.3 pin tip through J2.4 pin tip to the label.
    parts.append(_sch_wire(J6_PIN_X, J6_RX_Y, CONSOLE_LABEL_X, J6_RX_Y, "rx-bus"))
    parts.append(_sch_junction(J2_PIN_X, j2_rx_y, "rx-j2-tap"))
    parts.append(_sch_local_label(
        name="UART_RX", x=CONSOLE_LABEL_X, y=J6_RX_Y,
        angle=0, justify="left", uuid_tag="uart-rx-console",
    ))

    # ---- USB_DP / USB_DM: J6.13 / J6.14 → right hier labels ----
    # J6.13 USB_DP at Y=97.79, J6.14 USB_DM at Y=95.25 — both well NORTH
    # (above) of J2's Y range (118.11..130.81), so wires pass clear.
    parts.append(_sch_wire(J6_PIN_X, J6_USB_DP_Y, HLABEL_RIGHT_X, J6_USB_DP_Y, "usb-dp-bus"))
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
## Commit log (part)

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2026-05-11 kicad: add J1 power input terminal (24V+/GND/PE) to power sheet
    Adds the 3-pin pluggable input terminal J1 (Phoenix MSTBA
    2,5/3-G-5,08 footprint family). Pins 1/2/3 are wired to
    +24V / GND / Earth_Protective power flags, each backed by
    a PWR_FLAG sentinel so ERC sees the rails as externally
    driven. Embeds the five required lib_symbols
    (Screw_Terminal_01x03, +24V, GND, Earth_Protective,
2026-05-11 kicad: PTC fuse F1 + schematic render pipeline + power layout rework
    Three bundled changes to the power-input section:
    1. regenerate.py now exports every hierarchical sheet to
    renders/sch-<name>.{svg,png} via kicad-cli sch export svg.
    Gives reviewers and future agents a visual feedback loop
    for schematic edits, mirroring what we already have for
    PCB renders.
2026-05-11 kicad: TVS diode D1 (SMBJ24A) for surge protection on VIN
    Adds unidirectional TVS diode D1 in parallel between the J1
    pin 1 input (VIN, before Q1) and GND. Clamps transient
    over-voltage events to ~38.9V at 1A peak surge, keeping the
    downstream Q1 P-MOSFET (Vds_max = 40V) within its absolute
    maximum rating.
    SMBJ24A specifics:
2026-05-11 chore: gitignore __pycache__ directories
2026-05-11 docs: case verification checklist + CLAUDE.md v0.2 changelog
    Adds docs/CASE-VERIFICATION-CHECKLIST.md capturing every assumption
    in the current schematic/PCB that needs validation against the
    physical AK-N-94 enclosure when it arrives from the supplier. The
    notable open question is the 17 mm front-side height limit - the
    DXF annotation may be global or regional, and resolution affects
    cap footprint selection (SMD D-can vs radial through-hole).
2026-05-11 kicad: chunk #1h - second-review fixes (Q1 Zener clamp, L1 uprate, SS cap, PMV65XP)
    Applies four fixes from the second schematic review.
    BLOCKER (Q1 Vgs overdrive): Adds D3 (18V Zener) + R4 (1k series)
    gate-source clamp to Q1. Without the clamp, Vgs at 24V supply
    sits at -24V - exceeds PMV65XP/DMP4015SK3's Vgs_max +/-20V
    absolute maximum by 20%, eventually destroying the gate oxide.
    The Zener clamps |Vgs| to <=18V; R4 limits clamp current to
2026-05-12 kicad: D3 value field - include power rating (18V Zener 500mW)
    Closes the MEDIUM finding from the third review: D3's BOM value
    field previously read just '18V Zener', omitting the 500mW power
    rating that is part of the requirement. Without the rating in the
    BOM-visible field, there was a risk at PCB-layout time of picking
    a Zener with the wrong package (SOD-323 vs SOD-123) or insufficient
    power-handling for the worst-case clamping event.
2026-05-12 docs: v0.3 - drop external USB-C, pinout corrections, sourcing policy
    Captures three decisions made after the MCU research pass:
    1. External USB-C connector dropped from the design. Programming
    uses the ESP32-C6 SuperMini's onboard USB-C (accessible before
    enclosure is sealed); OTA via ESPHome+HA handles all updates
    after first flash. One fewer PCB cutout, cleaner exterior,
    one fewer BOM line. Optional unpopulated SWD/UART header may
2026-05-12 docs: KiCad schematic conventions + pre-fix verification rules
    Captures lessons learned from chunk #4 (MCU sub-sheet) and its
    follow-up J2-pinout fix:
    1. KiCad schematic conventions section explaining:
    - no_connect markers (small X on unused IC pins - ERC silencer
    documenting intentional non-connection)
    - DNP flag with (dnp yes) for hand-solder-on-demand parts like
2026-05-12 docs: relax back-side height limit 3 mm -> 5 mm via washer lift
    User decision: back-side clearance constraint relaxed from 3 mm
    (per DXF annotation '背面焊脚限高 3mm') to 5 mm effective. Achieved
    by adding 2 mm washers under the M3 mounting screws, which lifts
    the PCB off the enclosure's plastic mounting bosses by 2 mm.
    Rationale: standard through-hole pin headers (used for the J2
    recovery DNP footprint) protrude ~2.5-3 mm on the back side after
2026-05-12 docs: v0.4 - lock MCU module + Module identification rule + critical pinout fix
    Three updates in one commit:
    1. **MCU module locked to ESP32-C6-DevKitM-1-N4** (Espressif official
    devkit). EAN 5904422385651 (Botland), SKU ESP32-C6-DevKitM-1-N4.
    Chosen over generic 'SuperMini' clones because:
    - Branded with deterministic, documented pinout
    - Full Espressif documentation available
2026-05-12 docs: correct DevKitM-1-N4 USB description (TWO USB-C, not one)
    Earlier v0.4 commits incorrectly stated the ESP32-C6-DevKitM-1-N4
    has 'single USB-C connector (no separate bridge IC)'. Verified by
    Playwright screenshot of the Botland product page and Espressif's
    official user guide: the board has TWO USB-C connectors:
    1. USB Type-C to UART Port - power + flash + comm via an onboard
    USB-to-UART bridge IC (classic flashing path, model not stated
2026-05-17 docs: sk6812-side.md lead text Twelve -> Eleven (D14 vacated v0.18)
2026-05-22 Revert "feat(routing): v0.50 full routing rework — Freerouting + grid-A* + GND stitch"
    This reverts commit dd98a8b5e2c532be2b86d95f3e04231419d46720.
2026-06-09 v0.52: code-review remediation — unit tests, Lesson 12/20 enforcement, exit codes, README
    - tools/extract_routes.py: resolve net references in BOTH formats
    ((net N "name") KiCad-save and boardgen's (net N) via the board's
    net-declaration table, loud failure on unknown codes); refuse to
    overwrite oas_routes.py on a zero-record extraction (Lesson 12 closed)
    - hardware/kicad/tests/: first unit-test suite (48 tests) — UUID
    determinism (Lesson 9), fmt(), D-shape/mounting-hole/LED-ring geometry

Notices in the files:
README.md:
License: GPLv3
